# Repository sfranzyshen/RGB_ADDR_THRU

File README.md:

Textile mounting PCB for rgb addressable through-hole leds
# RGB_ADDR_THRU

#oshpark.com - order pcb
https://oshpark.com/shared_projects/9qCxvAe7

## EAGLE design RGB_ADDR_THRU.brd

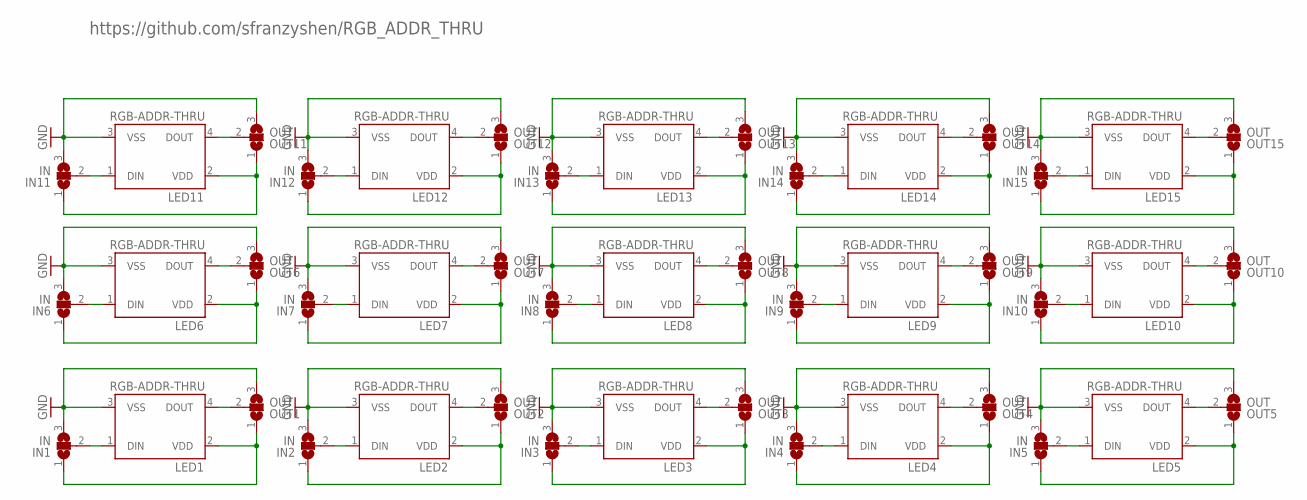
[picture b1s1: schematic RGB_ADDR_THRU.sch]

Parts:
IN1, IN2, IN3, IN4, IN5, IN6, IN7, IN8, IN9, IN10, IN11, IN12, IN13, IN14, IN15: IN; SJ_2W
LED1, LED2, LED3, LED4, LED5, LED6, LED7, LED8, LED9, LED10, LED11, LED12, LED13, LED14, LED15: RGB-ADDR-THRU; LED-RGB-THRU
OUT1, OUT2, OUT3, OUT4, OUT5, OUT6, OUT7, OUT8, OUT9, OUT10, OUT11, OUT12, OUT13, OUT14, OUT15: OUT; SJ_2W

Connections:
GND: IN1.3, IN2.3, IN3.3, IN4.3, IN5.3, IN6.3, IN7.3, IN8.3, IN9.3, IN10.3, IN11.3, IN12.3, IN13.3, IN14.3, IN15.3, LED1.3 (VSS), LED2.3 (VSS), LED3.3 (VSS), LED4.3 (VSS), LED5.3 (VSS), LED6.3 (VSS), LED7.3 (VSS), LED8.3 (VSS), LED9.3 (VSS), LED10.3 (VSS), LED11.3 (VSS), LED12.3 (VSS), LED13.3 (VSS), LED14.3 (VSS), LED15.3 (VSS), OUT1.3, OUT2.3, OUT3.3, OUT4.3, OUT5.3, OUT6.3, OUT7.3, OUT8.3, OUT9.3, OUT10.3, OUT11.3, OUT12.3, OUT13.3, OUT14.3, OUT15.3
unnamed: IN1.2, LED1.1 (DIN)
unnamed: IN1.1, LED1.2 (VDD), OUT1.1
unnamed: LED1.4 (DOUT), OUT1.2
unnamed: IN2.2, LED2.1 (DIN)
unnamed: IN2.1, LED2.2 (VDD), OUT2.1
unnamed: LED2.4 (DOUT), OUT2.2
unnamed: IN7.2, LED7.1 (DIN)
unnamed: IN7.1, LED7.2 (VDD), OUT7.1
unnamed: LED7.4 (DOUT), OUT7.2
unnamed: IN8.2, LED8.1 (DIN)
unnamed: IN8.1, LED8.2 (VDD), OUT8.1
unnamed: LED8.4 (DOUT), OUT8.2
unnamed: IN9.2, LED9.1 (DIN)
unnamed: IN9.1, LED9.2 (VDD), OUT9.1
unnamed: LED9.4 (DOUT), OUT9.2
unnamed: IN3.2, LED3.1 (DIN)
unnamed: IN3.1, LED3.2 (VDD), OUT3.1
unnamed: LED3.4 (DOUT), OUT3.2
unnamed: IN10.2, LED10.1 (DIN)
unnamed: IN10.1, LED10.2 (VDD), OUT10.1
unnamed: LED10.4 (DOUT), OUT10.2
unnamed: IN4.2, LED4.1 (DIN)
unnamed: IN4.1, LED4.2 (VDD), OUT4.1
unnamed: LED4.4 (DOUT), OUT4.2
unnamed: IN5.2, LED5.1 (DIN)
unnamed: IN5.1, LED5.2 (VDD), OUT5.1
unnamed: LED5.4 (DOUT), OUT5.2
unnamed: IN6.2, LED6.1 (DIN)
unnamed: IN6.1, LED6.2 (VDD), OUT6.1
unnamed: LED6.4 (DOUT), OUT6.2
unnamed: IN11.2, LED11.1 (DIN)
unnamed: IN11.1, LED11.2 (VDD), OUT11.1
unnamed: LED11.4 (DOUT), OUT11.2
unnamed: IN12.2, LED12.1 (DIN)
unnamed: IN12.1, LED12.2 (VDD), OUT12.1
unnamed: LED12.4 (DOUT), OUT12.2
unnamed: IN13.2, LED13.1 (DIN)
unnamed: IN13.1, LED13.2 (VDD), OUT13.1
unnamed: LED13.4 (DOUT), OUT13.2
unnamed: IN14.2, LED14.1 (DIN)
unnamed: IN14.1, LED14.2 (VDD), OUT14.1
unnamed: LED14.4 (DOUT), OUT14.2
unnamed: IN15.2, LED15.1 (DIN)
unnamed: IN15.1, LED15.2 (VDD), OUT15.1
unnamed: LED15.4 (DOUT), OUT15.2

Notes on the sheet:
https://github.com/sfranzyshen/RGB_ADDR_THRU

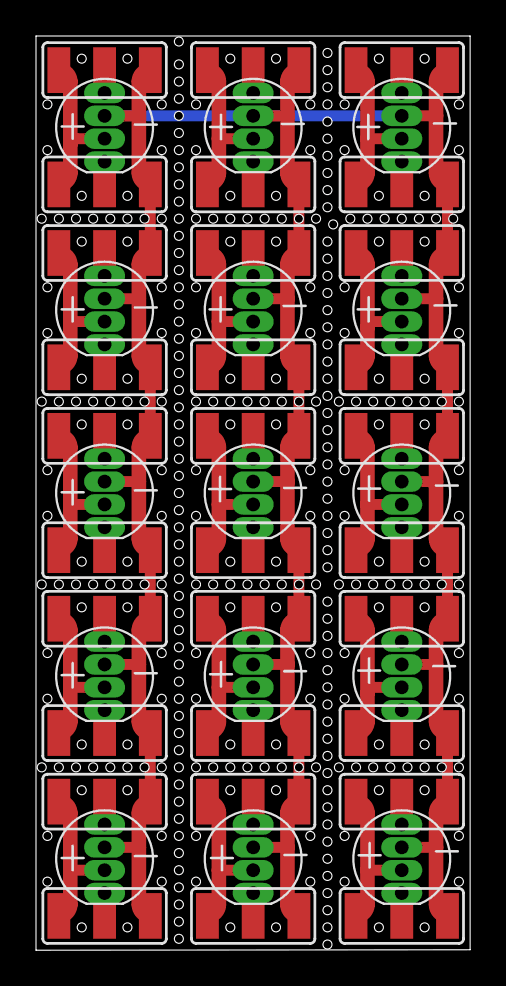
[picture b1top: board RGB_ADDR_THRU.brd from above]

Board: 2 copper layers, 24.1 x 50.8 mm, 45 parts (0 on the bottom side), 46 nets.

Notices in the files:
parts and their libraries:
SparkFun-LED: Licensing: Creative Commons ShareAlike 4.0 International - https://creativecommons.org/licenses/by-sa/4.0
